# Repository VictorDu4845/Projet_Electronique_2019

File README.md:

# Projet_Electronique_2019

## Groupe n°8 

CONDE Ibrahima

LIBER Maxime

MICHAUX Victor

VIROUX Nicolas

## Description du projet :

Le but de ce projet est de réaliser une sonde de températue à base d'un microcontroleur PIC. Le principe est de récupérer un signal analogique et de traduire ce signal afin de l'afficher sur deux afficheurs 7 segments.

Pour mieux s'organiser, nous avons utilisé [Trello](https://trello.com/b/IhGVI2MF/projet)

## Langage de programmation utilisé :

> C

> Java

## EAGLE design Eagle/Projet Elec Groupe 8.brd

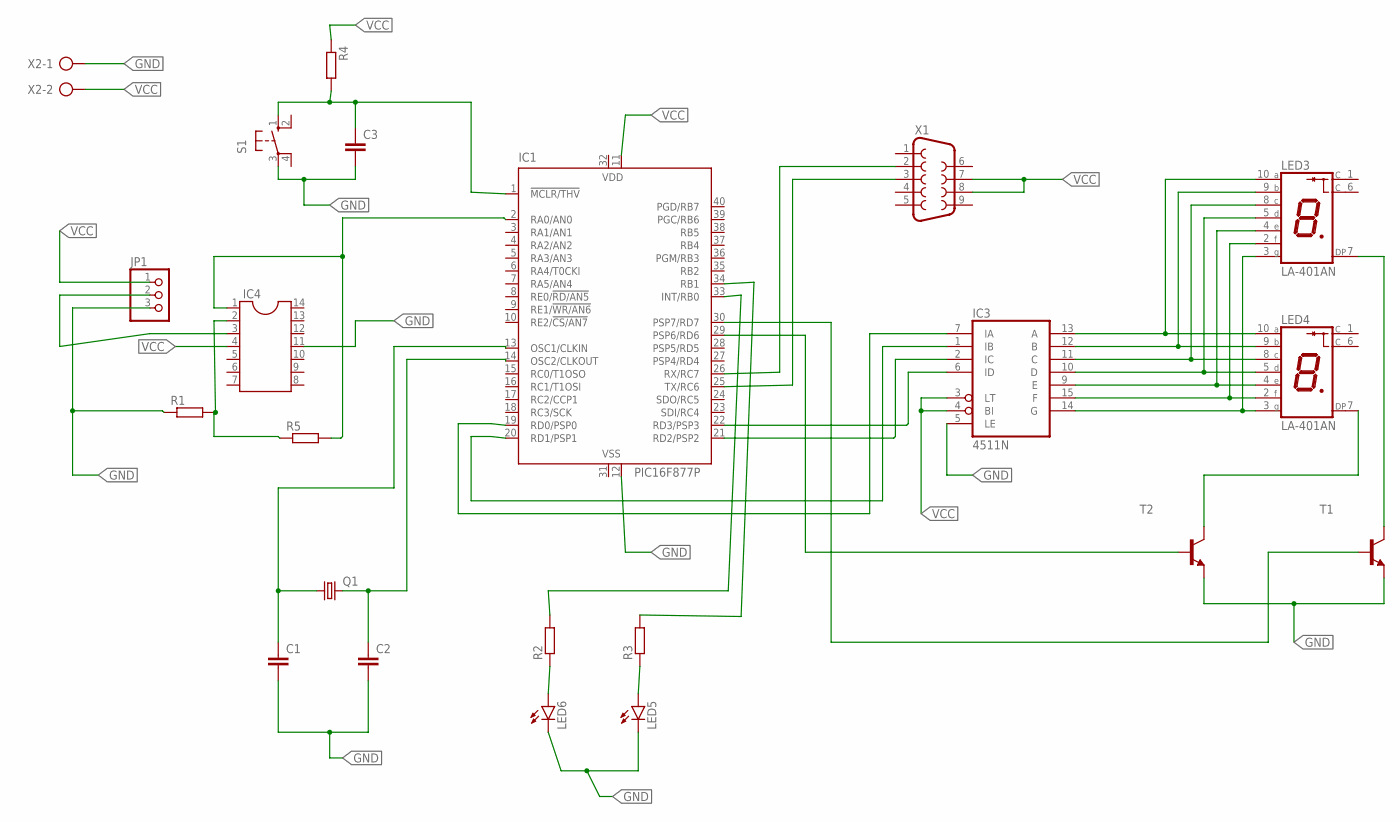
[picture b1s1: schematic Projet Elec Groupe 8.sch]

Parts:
C1, C2, C3: C-EU025-025X050; C025-025X050
IC1: PIC16F877P; DIL40
IC3: 4511N; DIL16
IC4: DIL14
JP1: PINHD-1X3; 1X03
LED3, LED4: LA-401AN; LA-401
LED5, LED6: LEDLD260; LD260
Q1: CRYSTALHC18U-V; HC18U-V
R1, R2, R3, R4, R5: R-EU_0204/5; 0204/5
S1: 10-XX; B3F-10XX
T1, T2: -NPN-TO92-EBC; TO92-EBC
X1: F09V
X2: AK300/2

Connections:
GND: C1.2, C2.2, C3.2, IC1.12 (VSS), IC3.5 (LE), IC4.11, JP1.3, LED5.K (C), LED6.K (C), R1.1, S1.3, T1.E, T2.E, X2.1
unnamed: IC1.30 (PSP7/RD7), T1.B
unnamed: IC1.29 (PSP6/RD6), T2.B
unnamed: IC3.13 (A), LED3.10 (A), LED4.10 (A)
unnamed: IC3.12 (B), LED3.9 (B), LED4.9 (B)
unnamed: IC3.11 (C), LED3.8 (C), LED4.8 (C)
unnamed: IC3.10 (D), LED3.5 (D), LED4.5 (D)
unnamed: IC3.9 (E), LED3.4 (E), LED4.4 (E)
unnamed: IC3.15 (F), LED3.2 (F), LED4.2 (F)
unnamed: IC3.14 (G), LED3.3 (G), LED4.3 (G)
unnamed: LED4.7 (DP), T2.C
unnamed: LED3.7 (DP), T1.C
unnamed: C1.1, IC1.13 (OSC1/CLKIN), Q1.1
unnamed: C2.1, IC1.14 (OSC2/CLKOUT), Q1.2
unnamed: LED6.A, R2.1
unnamed: LED5.A, R3.1
unnamed: IC1.26 (RX/RC7), X1.2
unnamed: IC1.19 (RD0/PSP0), IC3.7 (IA)
unnamed: IC1.20 (RD1/PSP1), IC3.1 (IB)
unnamed: IC1.21 (RD2/PSP2), IC3.2 (IC)
unnamed: IC1.22 (RD3/PSP3), IC3.6 (ID)
unnamed: C3.1, IC1.1 (!MCLR/THV), R4.2, S1.1 (S)
unnamed: IC4.3, JP1.2
unnamed: IC4.2, R1.2, R5.1
unnamed: IC1.2 (RA0/AN0), IC4.1, R5.2
unnamed: IC1.25 (TX/RC6), X1.3
unnamed: IC1.33 (INT/RB0), R2.2
unnamed: IC1.34 (RB1), R3.2
VCC: IC1.11 (VDD), IC3.3 (LT), IC3.4 (BI), IC4.4, JP1.1, R4.1, X1.7, X1.8, X2.2
VDD: IC1.32 (VDD), IC3.16 (VDD)
VSS: IC1.31 (VSS), IC3.8 (VSS)

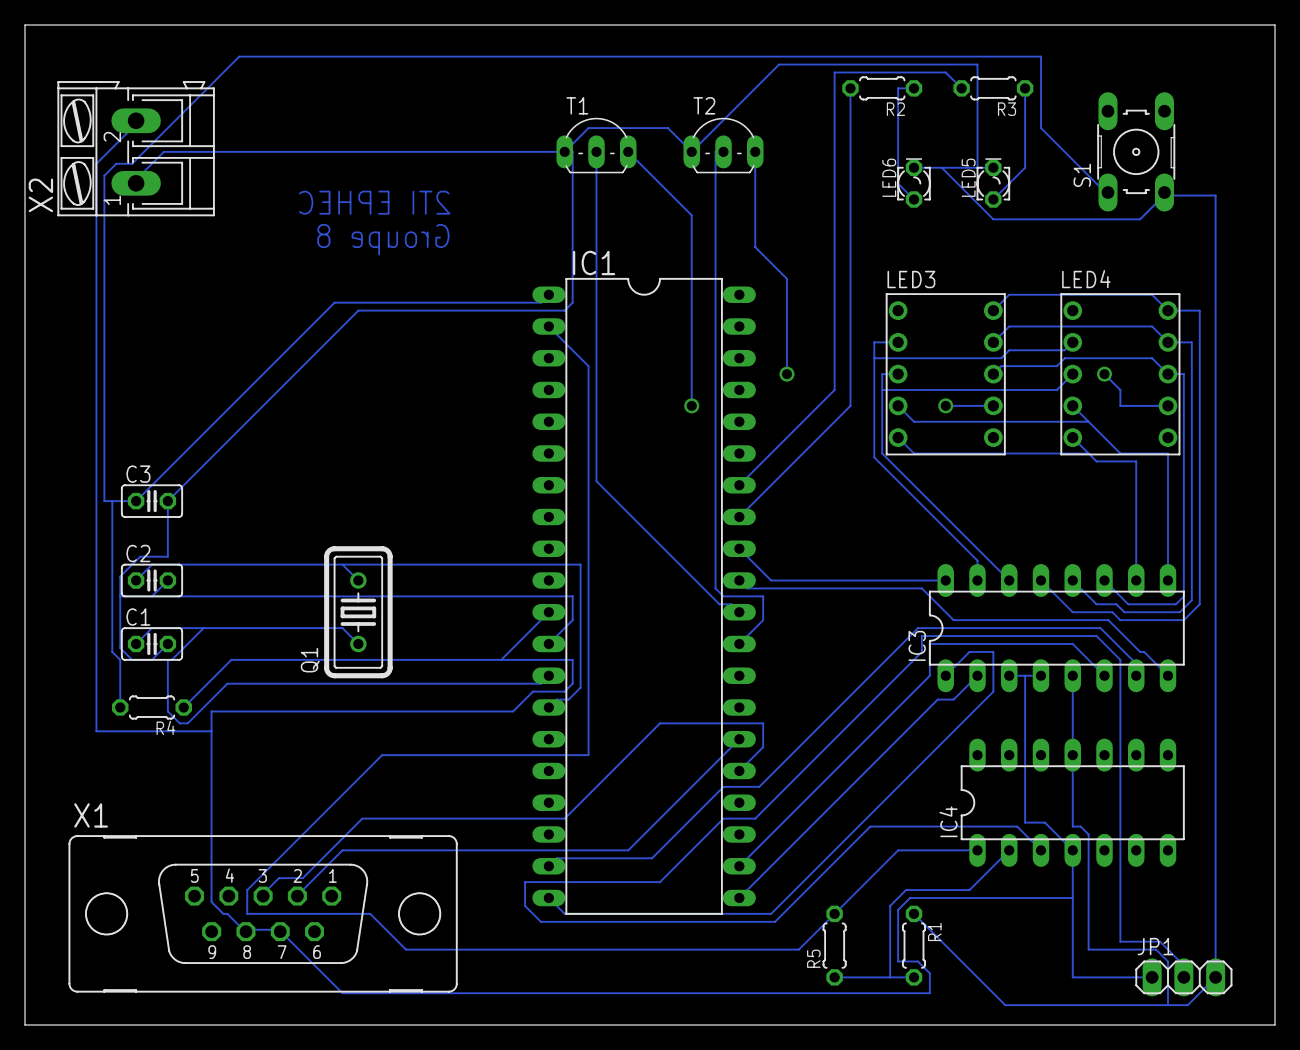
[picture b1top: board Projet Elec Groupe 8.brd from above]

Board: 2 copper layers, 100.0 x 80.0 mm, 22 parts (0 on the bottom side), 31 nets.

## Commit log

2019-05-17 Create schemas
2019-05-17 Create prtoe
2019-05-17 Create groupe 8
2019-05-17 Create projet
2019-05-19 Create important
